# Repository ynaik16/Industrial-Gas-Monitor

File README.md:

# Industrial-Gas-Monitor
An ASIC design for tracking gas levels between two industrial grade gas sensors, within a specific range.

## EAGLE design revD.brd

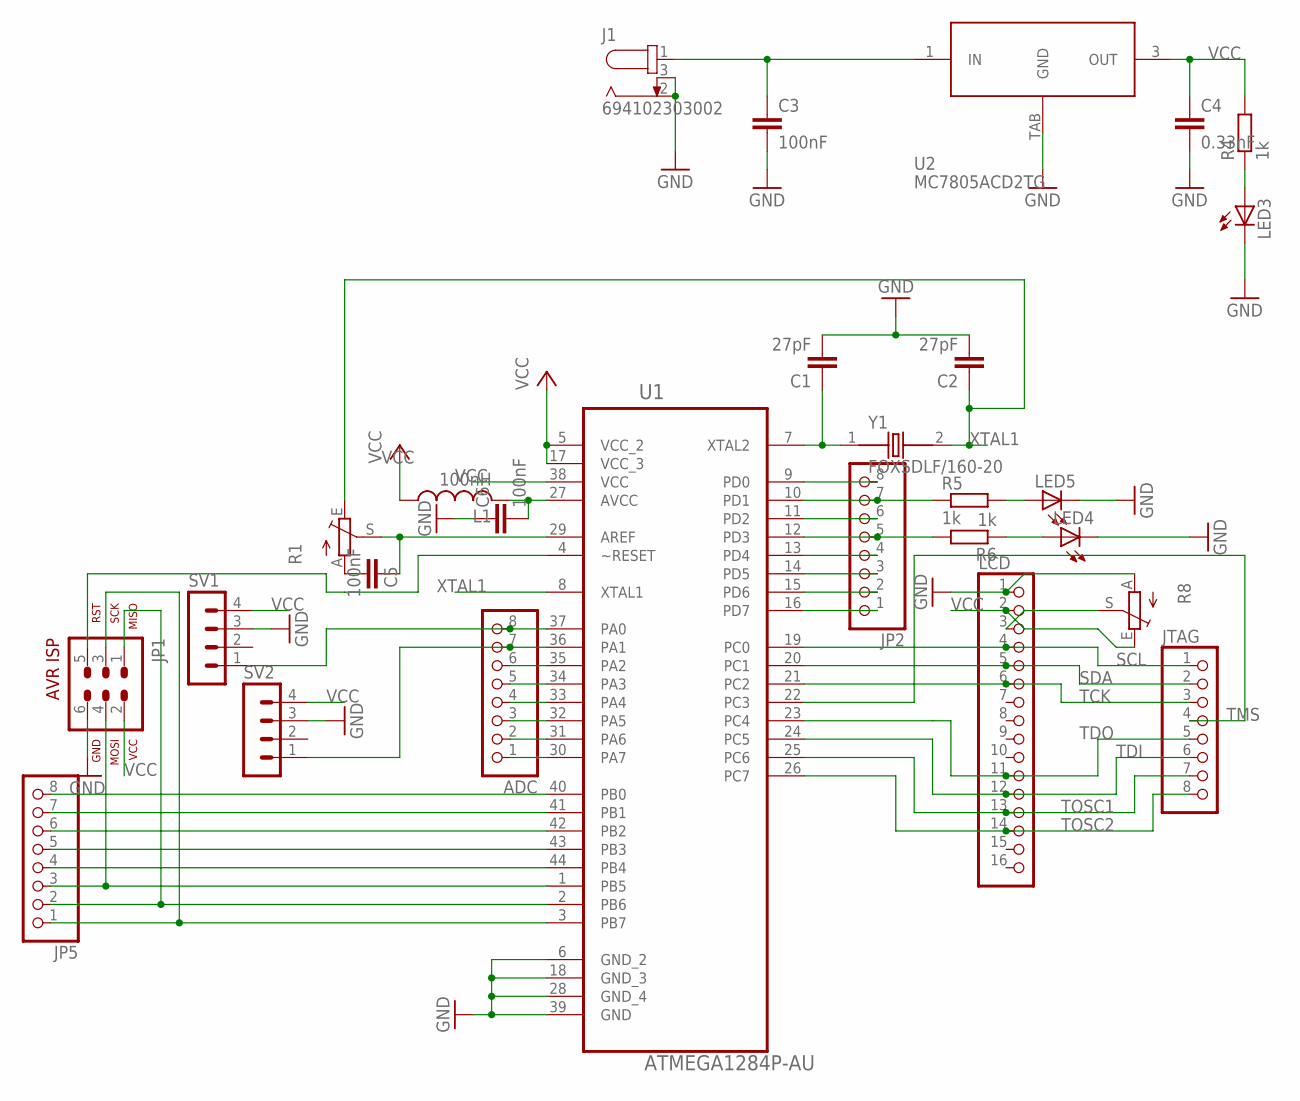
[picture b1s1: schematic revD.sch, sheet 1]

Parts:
ADC: PINHD-1X8; 1X08
C1, C2: 27pF; C1206
C3, C5, C6: 100nF; C1206
C4: 0.33nF; C1206
J1: 694102303002; 69410X303002
JP1: AVR-ISP-6VERT; AVR-ISP-6
JP2, JP5: PINHD-1X8; 1X08
JTAG: PINHD-1X8; 1X08
L1: 100nH; L1812
LCD: PINHD-1X16; 1X16
LED3, LED4, LED5: LED3MM
R1, R8: TRIM_1234-S64YW; S64YW
R4, R5, R6: 1k; M1206
SV1, SV2: MA04-1
U1: ATMEGA1284P-AU; QFP80P1200X1200X120-44N
U2: MC7805ACD2TG; D2PAK
Y1: FOXSDLF/160-20; XTAL_FOXSDLF/160-20

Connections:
GND: C1.2, C2.2, C3.2, C4.2, C6.1, J1.2, J1.3, JP1.6, LCD.1, LED3.K (C), LED4.K (C), LED5.K (C), R8.A, SV1.3, SV2.3, U1.6 (GND_2), U1.18 (GND_3), U1.28 (GND_4), U1.39 (GND), U2.TAB (GND); also elsewhere on the board
unnamed: C1.1, U1.7 (XTAL2), Y1.1
unnamed: C5.1, R1.S, U1.29 (AREF)
unnamed: C5.2, R1.A
unnamed: C6.2, L1.2, U1.27 (AVCC)
unnamed: C3.1, J1.1, U2.1 (IN)
unnamed: LED3.A, R4.1
unnamed: LED4.A, R6.1
unnamed: LED5.A, R5.2
unnamed: LCD.3, R8.S
unnamed: JP5.8, U1.40 (PB0)
unnamed: JP5.7, U1.41 (PB1)
unnamed: JP5.6, U1.42 (PB2)
unnamed: JP5.5, U1.43 (PB3)
unnamed: JP5.4, U1.44 (PB4)
unnamed: JP1.4, JP5.3, U1.1 (PB5)
unnamed: JP1.1, JP5.2, U1.2 (PB6)
unnamed: JP1.3, JP5.1, U1.3 (PB7)
unnamed: ADC.8, SV1.1, U1.37 (PA0)
unnamed: ADC.7, SV2.1, U1.36 (PA1)
unnamed: ADC.6, U1.35 (PA2)
unnamed: ADC.5, U1.34 (PA3)
unnamed: ADC.4, U1.33 (PA4)
unnamed: ADC.3, U1.32 (PA5)
unnamed: ADC.2, U1.31 (PA6)
unnamed: ADC.1, U1.30 (PA7)
unnamed: JP2.8, U1.9 (PD0)
unnamed: JP2.7, R5.1, U1.10 (PD1)
unnamed: JP2.6, U1.11 (PD2)
unnamed: JP2.5, R6.2, U1.12 (PD3)
unnamed: JP2.4, U1.13 (PD4)
unnamed: JP2.3, U1.14 (PD5)
unnamed: JP2.2, U1.15 (PD6)
unnamed: JP2.1, U1.16 (PD7)
unnamed: JP1.5, U1.4 (~RESET)
SCL: JTAG.1, LCD.4, U1.19 (PC0)
SDA: JTAG.2, LCD.5, U1.20 (PC1)
TCK: JTAG.3, LCD.6, U1.21 (PC2)
TDI: JTAG.6, LCD.12, U1.24 (PC5)
TDO: JTAG.5, LCD.11, U1.23 (PC4)
TMS: JTAG.4, U1.22 (PC3)
TOSC1: JTAG.7, LCD.13, U1.25 (PC6)
TOSC2: JTAG.8, LCD.14, U1.26 (PC7)
VCC: C4.1, JP1.2, L1.1, LCD.2, R4.2, R8.E, SV1.4, SV2.4, U1.5 (VCC_2), U1.17 (VCC_3), U1.38 (VCC), U2.3 (OUT); also elsewhere on the board
XTAL1: C2.1, R1.E, U1.8 (XTAL1), Y1.2

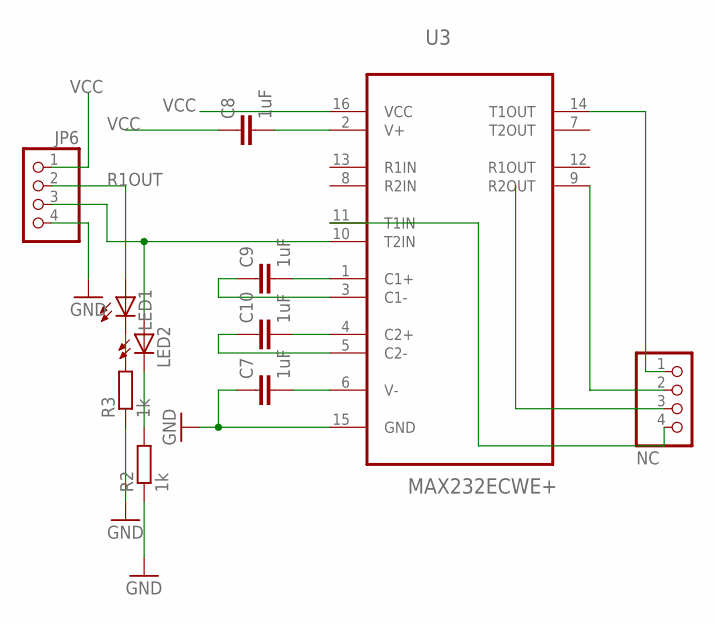
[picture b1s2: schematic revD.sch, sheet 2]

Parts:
C7, C8, C9, C10: 1uF; C1206
JP6: PINHD-1X4; 1X04
LED1, LED2: LEDSMT1206; 1206
NC: NC; 1X04
R2, R3: 1k; R1206
U3: MAX232ECWE+; SOIC127P1032X265-16N

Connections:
GND: C7.1, JP6.4, R2.1, R3.1, U3.15 (GND); also elsewhere on the board
unnamed: C8.2, U3.2 (V+)
unnamed: C7.2, U3.6 (V-)
unnamed: C10.2, U3.4 (C2+)
unnamed: C10.1, U3.5 (C2-)
unnamed: C9.2, U3.1 (C1+)
unnamed: C9.1, U3.3 (C1-)
unnamed: JP6.3, LED2.A, U3.10 (T2IN)
unnamed: LED1.C, R3.2
unnamed: LED2.C, R2.2
unnamed: NC.1, U3.14 (T1OUT)
unnamed: NC.2, U3.9 (R2OUT)
unnamed: NC.4, U3.11 (T1IN)
R1OUT: JP6.2, LED1.A
VCC: C8.1, JP6.1, U3.16 (VCC); also elsewhere on the board

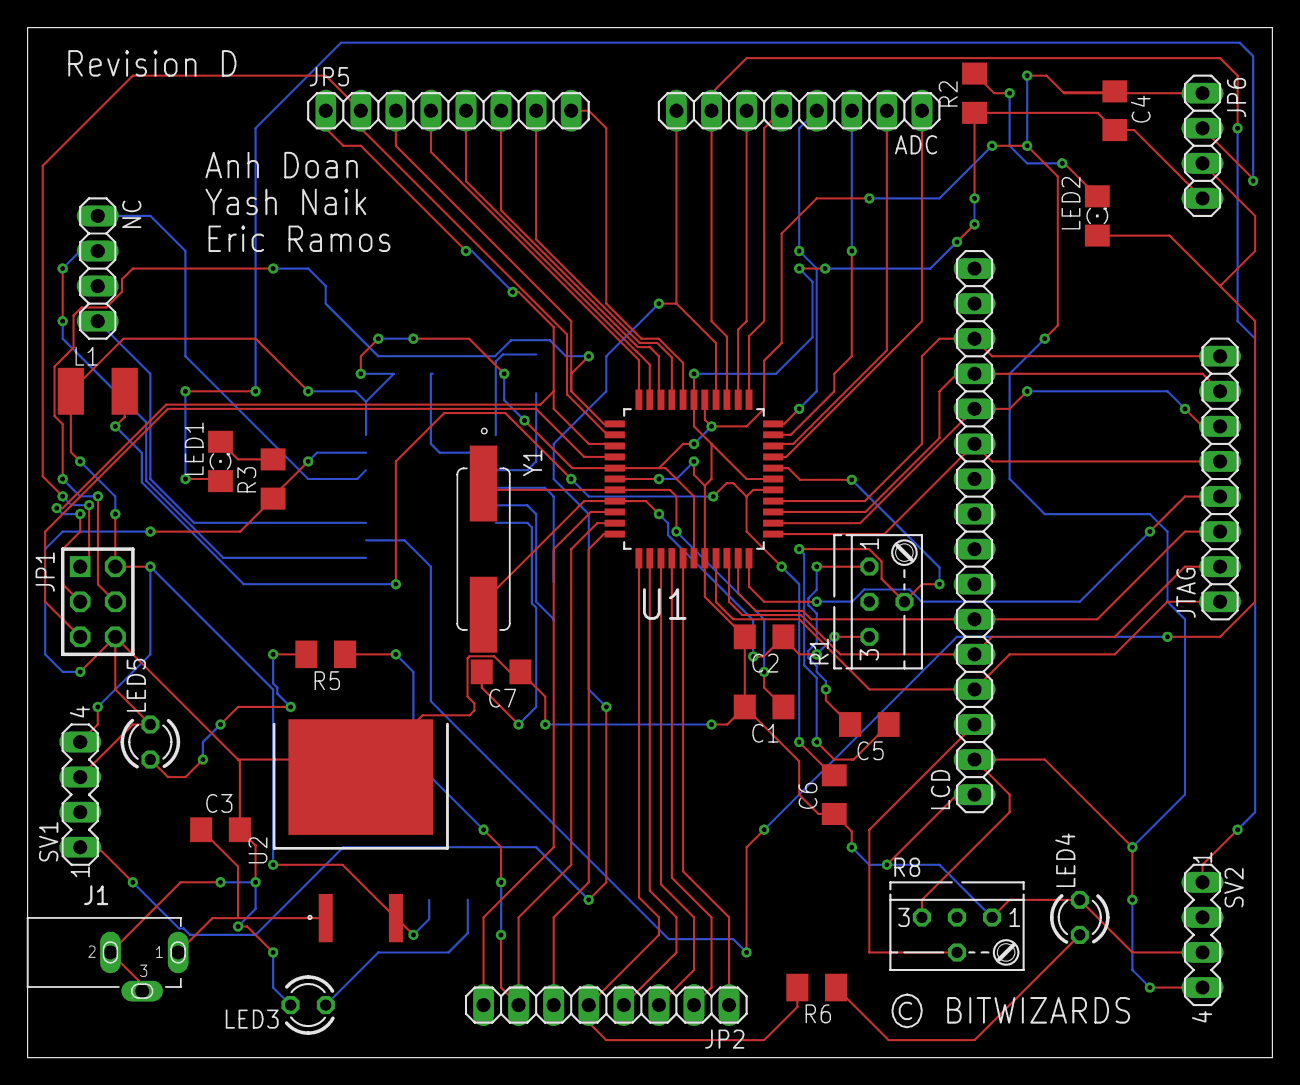
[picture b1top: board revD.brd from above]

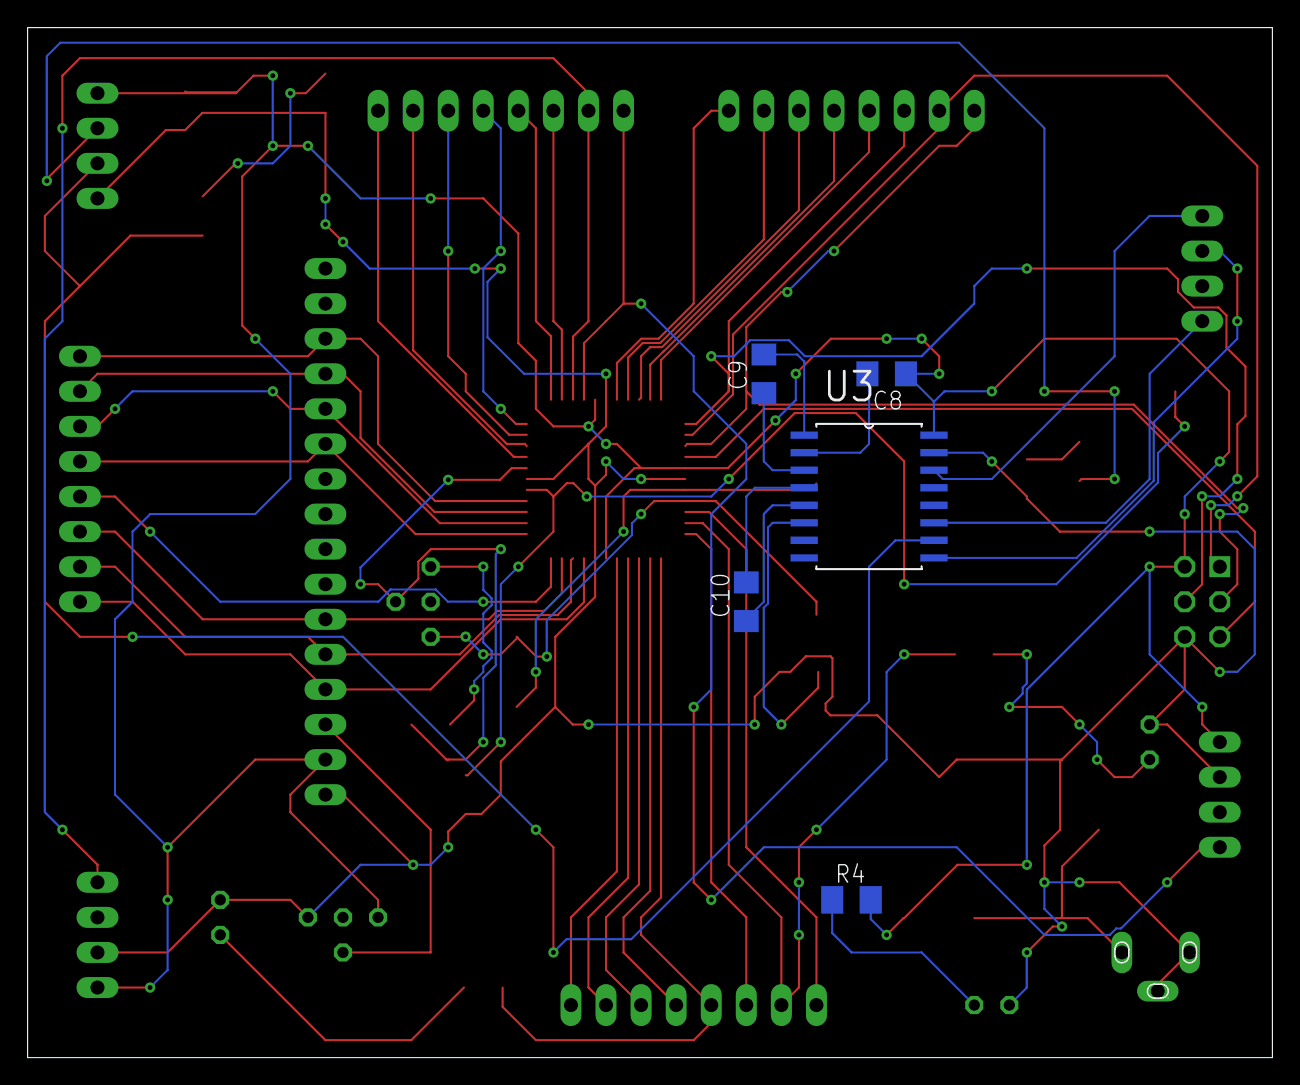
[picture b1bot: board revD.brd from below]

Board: 2 copper layers, 90.1 x 74.5 mm, 38 parts (5 on the bottom side), 58 nets.

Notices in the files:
revD.brd:
© BITWIZARDS
